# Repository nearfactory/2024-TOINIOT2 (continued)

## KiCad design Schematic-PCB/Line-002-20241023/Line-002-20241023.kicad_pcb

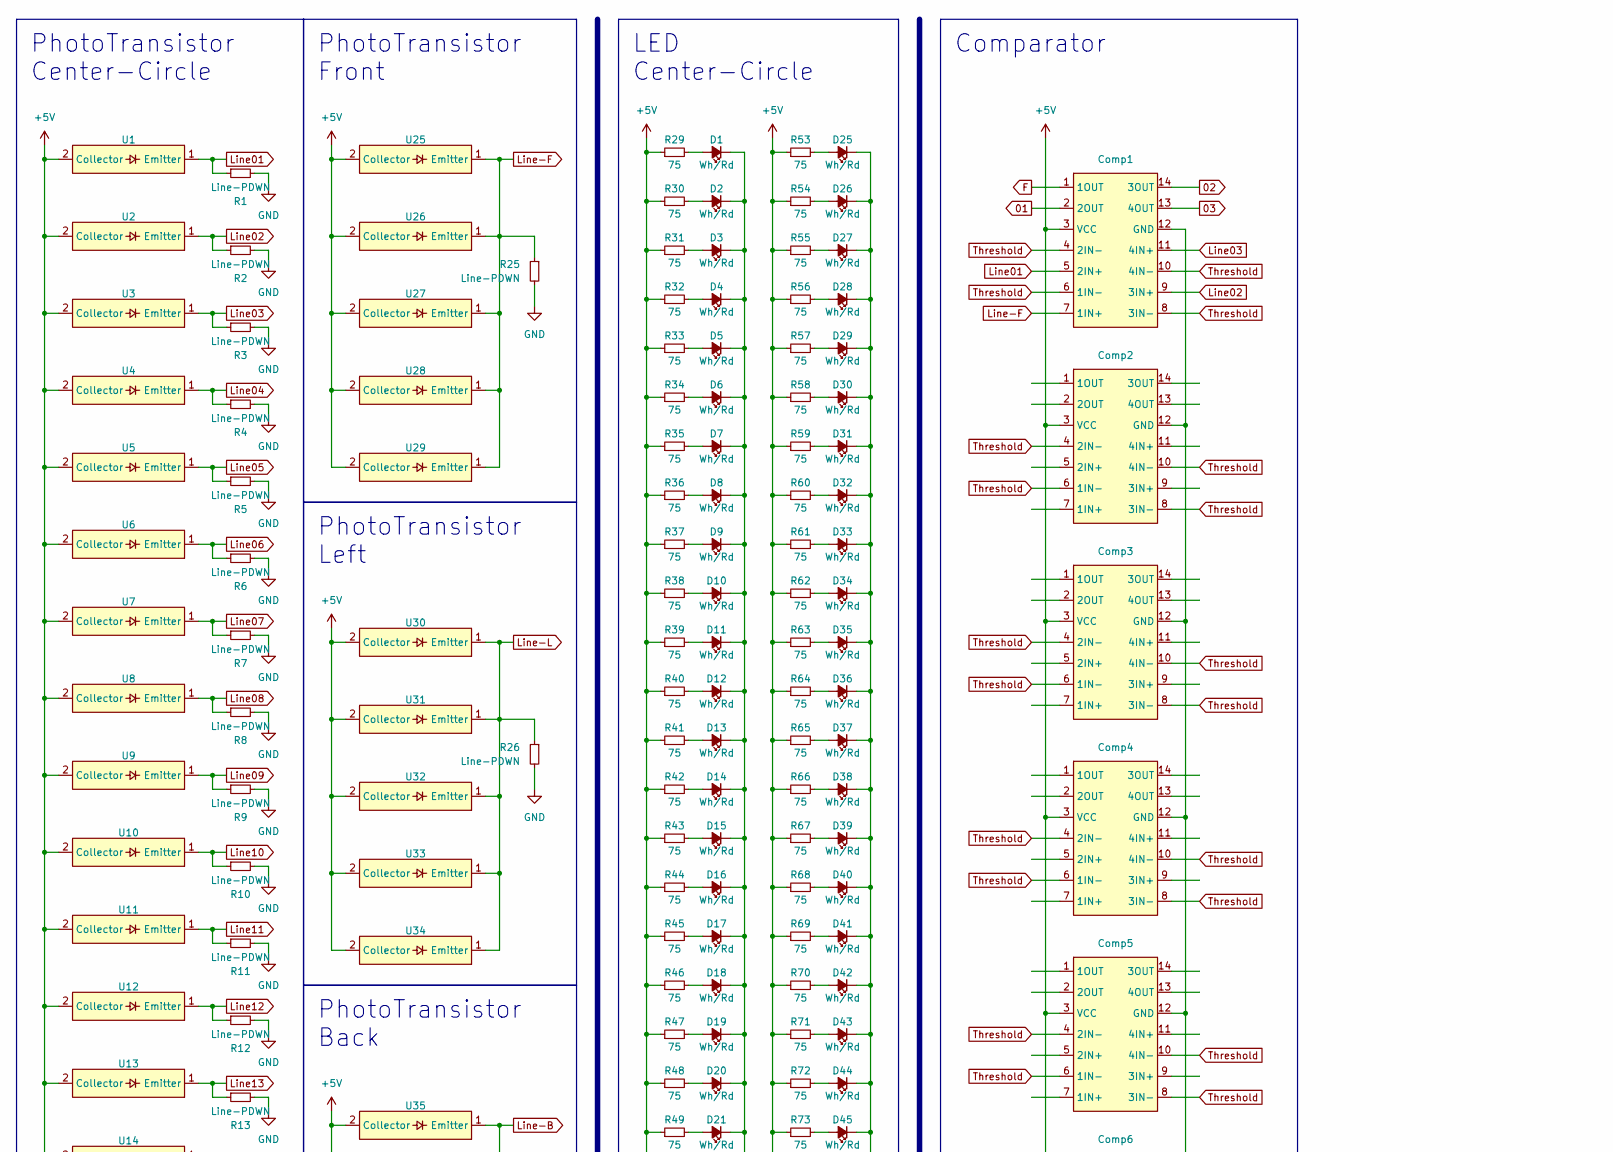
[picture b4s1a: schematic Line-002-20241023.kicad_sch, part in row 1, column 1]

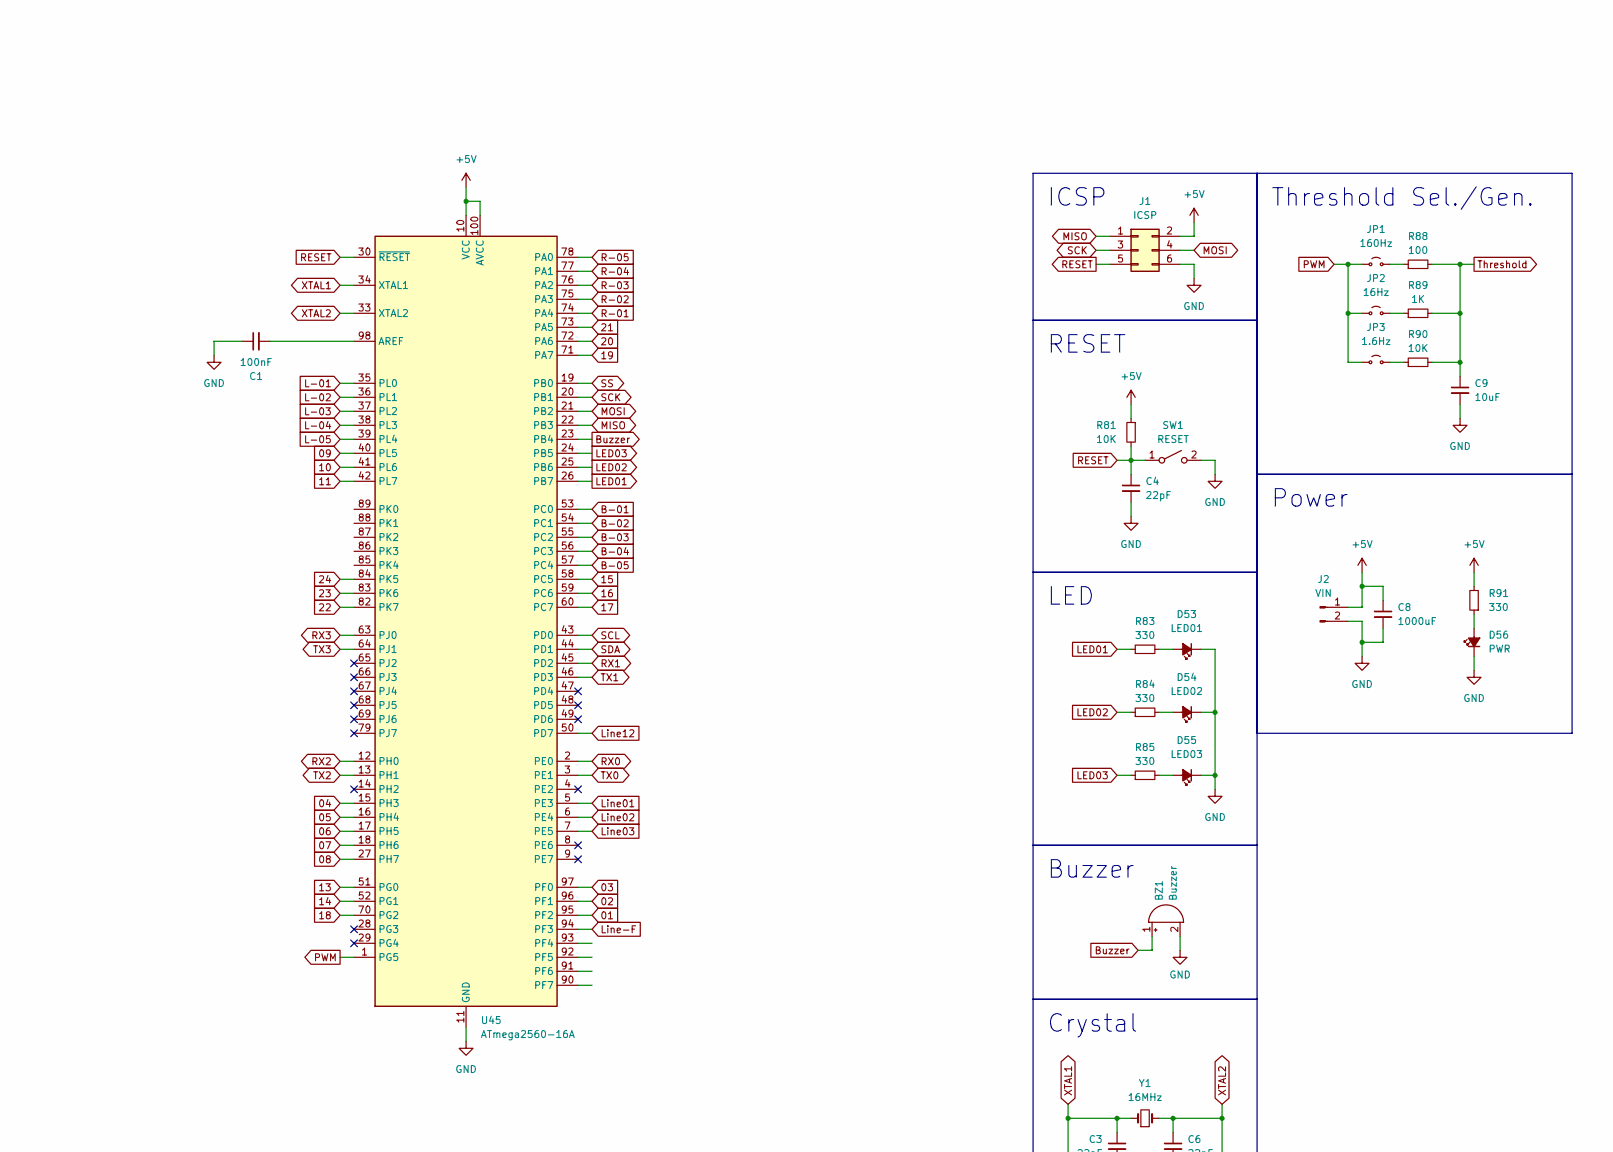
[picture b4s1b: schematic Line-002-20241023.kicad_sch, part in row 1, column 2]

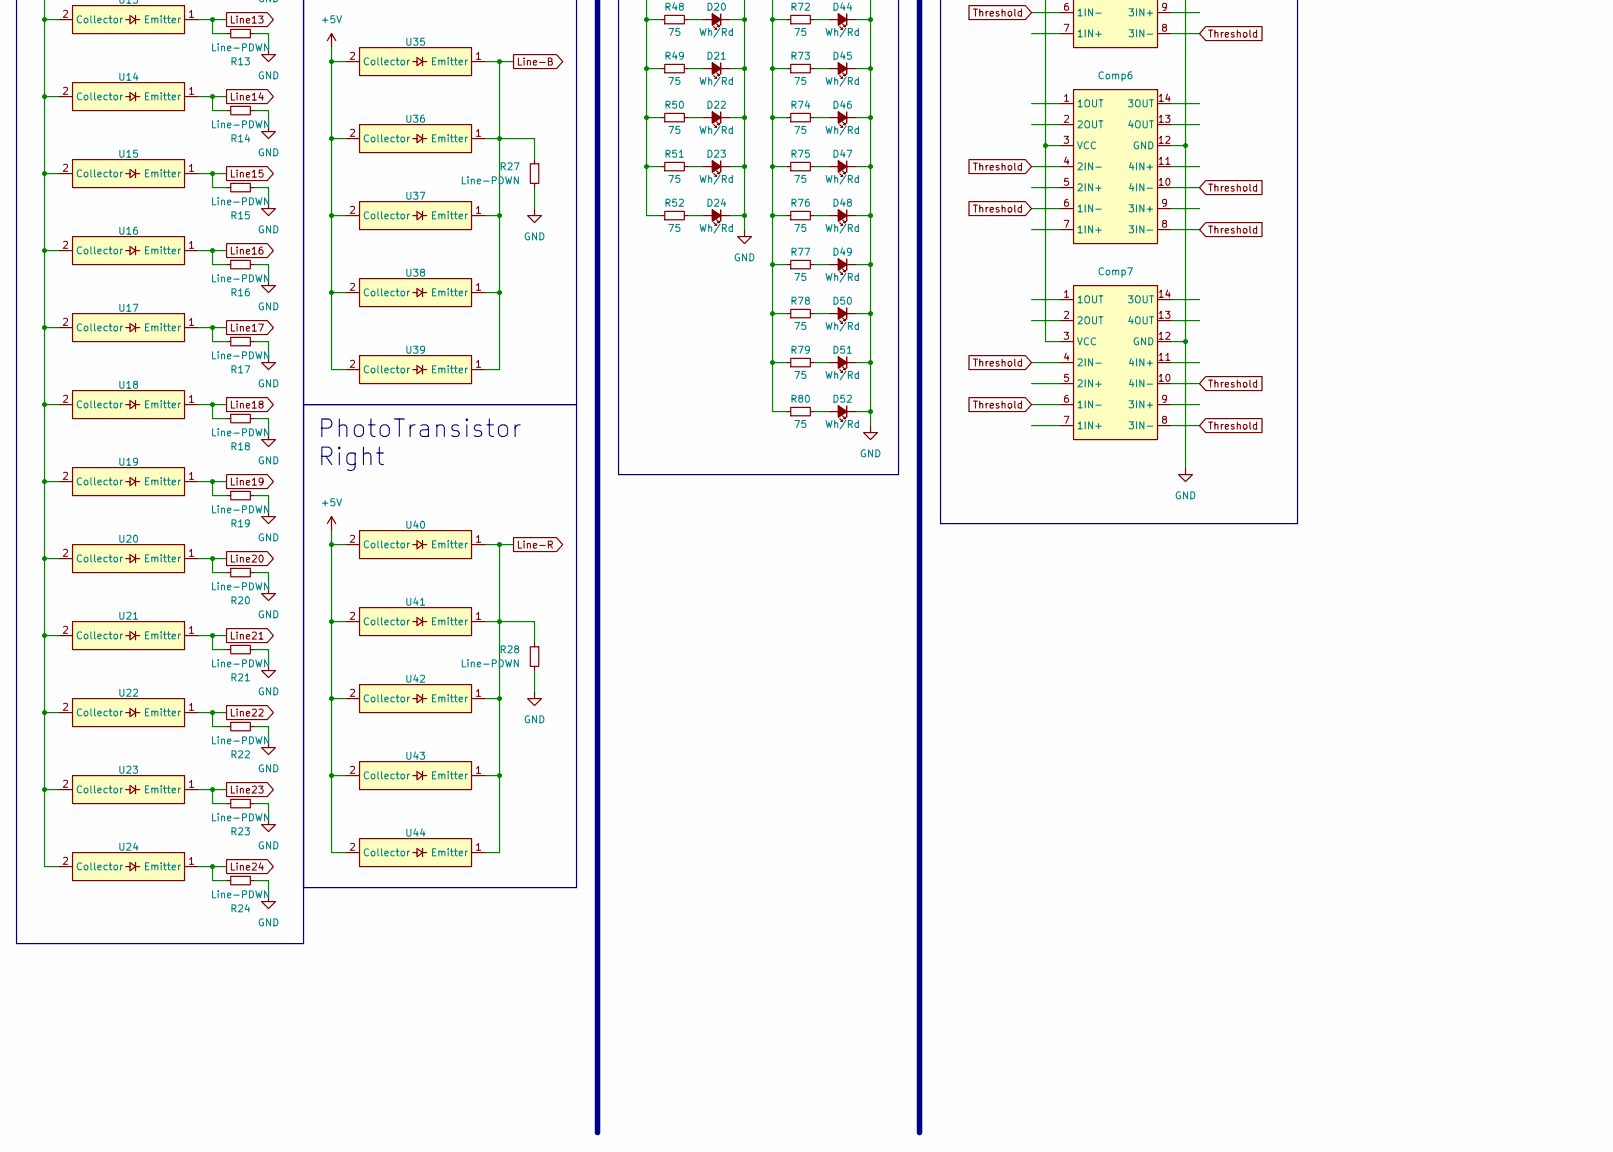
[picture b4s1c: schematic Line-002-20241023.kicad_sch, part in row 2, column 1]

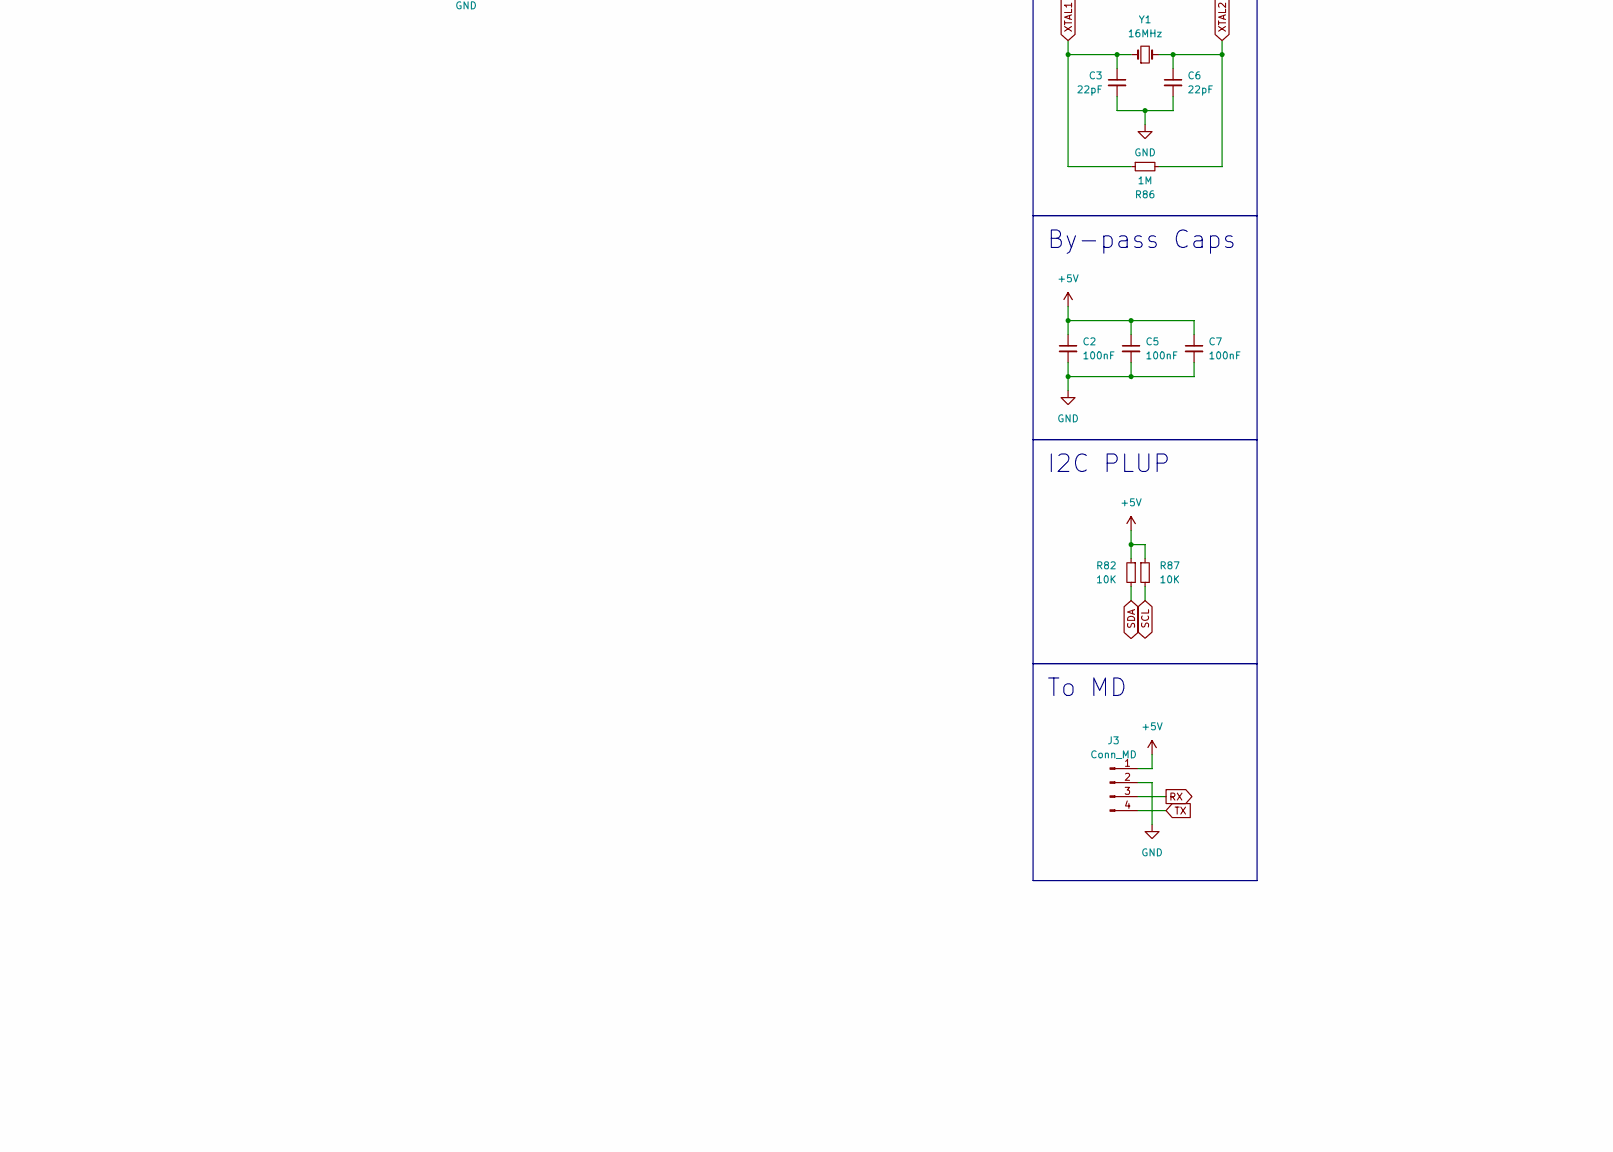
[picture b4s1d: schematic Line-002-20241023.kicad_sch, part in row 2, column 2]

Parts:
BZ1: Buzzer; PKM13EPYH4000-A0
C1, C2, C5, C7: 100nF; C_0603_1608Metric
C3, C4, C6: 22pF; C_0603_1608Metric
C8: 1000uF; C_0603_1608Metric
C9: 10uF; C_0805_2012Metric
Comp1, Comp2, Comp3, Comp4, Comp5, Comp6, Comp7: (no value)
D1, D2, D3, D4, D5, D6, D7, D8, D9, D10, D11, D12, D13, D14, D15, D16, D17, D18, D19, D20, D21, D22, D23, D24, D25, D26, D27, D28, D29, D30, D31, D32, D33, D34, D35, D36, D37, D38, D39, D40, D41, D42, D43, D44, D45, D46, D47, D48, D49, D50, D51, D52: Wh/Rd; LED-3mm
D53: LED01; LED_0603_1608Metric
D54: LED02; LED_0603_1608Metric
D55: LED03; LED_0603_1608Metric
D56: PWR; LED_0603_1608Metric
J1: ICSP; PinHeader_2x03_P2.54mm_Vertical
J2: VIN; JST_VH_B2P-VH-B_1x02_P3.96mm_Vertical
J3: Conn_MD
JP1: 160Hz; SolderJumper-2_P1.3mm_Open_Pad1.0x1.5mm
JP2: 16Hz; SolderJumper-2_P1.3mm_Open_Pad1.0x1.5mm
JP3: 1.6Hz; SolderJumper-2_P1.3mm_Open_Pad1.0x1.5mm
R1, R2, R3, R4, R5, R6, R7, R8, R9, R10, R11, R12, R13, R14, R15, R16, R17, R18, R19, R20, R21, R22, R23, R24, R25, R26, R27, R28: Line-PDWN; R_0603_1608Metric
R29, R30, R31, R32, R33, R34, R35, R36, R37, R38, R39, R40, R41, R42, R43, R44, R45, R46, R47, R48, R49, R50, R51, R52, R53, R54, R55, R56, R57, R58, R59, R60, R61, R62, R63, R64, R65, R66, R67, R68, R69, R70, R71, R72, R73, R74, R75, R76, R77, R78, R79, R80: 75; R_0603_1608Metric
R81, R82, R87, R90: 10K; R_0603_1608Metric
R83, R84, R85, R91: 330; R_0603_1608Metric
R86: 1M; R_0603_1608Metric
R88: 100; R_0603_1608Metric
R89: 1K; R_0603_1608Metric
SW1: RESET
U1, U2, U3, U4, U5, U6, U7, U8, U9, U10, U11, U12, U13, U14, U15, U16, U17, U18, U19, U20, U21, U22, U23, U24, U25, U26, U27, U28, U29, U30, U31, U32, U33, U34, U35, U36, U37, U38, U39, U40, U41, U42, U43, U44: NJL7502L
U45: ATmega2560-16A; TQFP-100_14x14mm_P0.5mm
Y1: 16MHz; AL4BT

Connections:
01: Comp1.2 (2OUT), U45.95 (PF2)
02: Comp1.14 (3OUT), U45.96 (PF1)
03: Comp1.13 (4OUT), U45.97 (PF0)
04: U45.15 (PH3)
05: U45.16 (PH4)
06: U45.17 (PH5)
07: U45.18 (PH6)
08: U45.27 (PH7)
09: U45.40 (PL5)
10: U45.41 (PL6)
11: U45.42 (PL7)
13: U45.51 (PG0)
14: U45.52 (PG1)
15: U45.58 (PC5)
16: U45.59 (PC6)
17: U45.60 (PC7)
18: U45.70 (PG2)
19: U45.71 (PA7)
20: U45.72 (PA6)
21: U45.73 (PA5)
22: U45.82 (PK7)
23: U45.83 (PK6)
24: U45.84 (PK5)
+5V: C2.1, C5.1, C7.1, C8.1, Comp1.3 (VCC), Comp2.3 (VCC), Comp3.3 (VCC), Comp4.3 (VCC), Comp5.3 (VCC), Comp6.3 (VCC), Comp7.3 (VCC), J1.2, J2.1, J3.1, R29.1, R30.1, R31.1, R32.1, R33.1, R34.1, R35.1, R36.1, R37.1, R38.1, R39.1, R40.1, R41.1, R42.1, R43.1, R44.1, R45.1, R46.1, R47.1, R48.1, R49.1, R50.1, R51.1, R52.1, R53.1, R54.1, R55.1, R56.1, R57.1, R58.1, R59.1, R60.1, R61.1, R62.1, R63.1, R64.1, R65.1, R66.1, R67.1, R68.1, R69.1, R70.1, R71.1, R72.1, R73.1, R74.1, R75.1, R76.1, R77.1, R78.1, R79.1, R80.1, R81.1, R82.1, R87.1, R91.2, U1.2 (Collector), U2.2 (Collector), U3.2 (Collector), U4.2 (Collector), U5.2 (Collector), U6.2 (Collector), U7.2 (Collector), U8.2 (Collector), U9.2 (Collector), U10.2 (Collector), U11.2 (Collector), U12.2 (Collector), U13.2 (Collector), U14.2 (Collector), U15.2 (Collector), U16.2 (Collector), U17.2 (Collector), U18.2 (Collector), U19.2 (Collector), U20.2 (Collector), U21.2 (Collector), U22.2 (Collector), U23.2 (Collector), U24.2 (Collector), U25.2 (Collector), U26.2 (Collector), U27.2 (Collector), U28.2 (Collector), U29.2 (Collector), U30.2 (Collector), U31.2 (Collector), U32.2 (Collector), U33.2 (Collector), U34.2 (Collector), U35.2 (Collector), U36.2 (Collector), U37.2 (Collector), U38.2 (Collector), U39.2 (Collector), U40.2 (Collector), U41.2 (Collector), U42.2 (Collector), U43.2 (Collector), U44.2 (Collector), U45.10 (VCC), U45.31 (VCC), U45.61 (VCC), U45.80 (VCC), U45.100 (AVCC)
B-01: U45.53 (PC0)
B-02: U45.54 (PC1)
B-03: U45.55 (PC2)
B-04: U45.56 (PC3)
B-05: U45.57 (PC4)
Buzzer: BZ1.1 (+), U45.23 (PB4)
GND: BZ1.2 (-), C1.1, C2.2, C3.2, C4.2, C5.2, C6.2, C7.2, C8.2, C9.2, Comp1.12 (GND), Comp2.12 (GND), Comp3.12 (GND), Comp4.12 (GND), Comp5.12 (GND), Comp6.12 (GND), Comp7.12 (GND), D1.1 (K), D2.1 (K), D3.1 (K), D4.1 (K), D5.1 (K), D6.1 (K), D7.1 (K), D8.1 (K), D9.1 (K), D10.1 (K), D11.1 (K), D12.1 (K), D13.1 (K), D14.1 (K), D15.1 (K), D16.1 (K), D17.1 (K), D18.1 (K), D19.1 (K), D20.1 (K), D21.1 (K), D22.1 (K), D23.1 (K), D24.1 (K), D25.1 (K), D26.1 (K), D27.1 (K), D28.1 (K), D29.1 (K), D30.1 (K), D31.1 (K), D32.1 (K), D33.1 (K), D34.1 (K), D35.1 (K), D36.1 (K), D37.1 (K), D38.1 (K), D39.1 (K), D40.1 (K), D41.1 (K), D42.1 (K), D43.1 (K), D44.1 (K), D45.1 (K), D46.1 (K), D47.1 (K), D48.1 (K), D49.1 (K), D50.1 (K), D51.1 (K), D52.1 (K), D53.1 (K), D54.1 (K), D55.1 (K), D56.1 (K), J1.6, J2.2, J3.2, R1.2, R2.2, R3.2, R4.2, R5.2, R6.2, R7.2, R8.2, R9.2, R10.2, R11.2, R12.2, R13.2, R14.2, R15.2, R16.2, R17.2, R18.2, R19.2, R20.2, R21.2, R22.2, R23.2, R24.2, R25.2, R26.2, R27.2, R28.2, SW1.2 (B), U45.11 (GND), U45.32 (GND), U45.62 (GND), U45.81 (GND), U45.99 (GND)
L-01: U45.35 (PL0)
L-02: U45.36 (PL1)
L-03: U45.37 (PL2)
L-04: U45.38 (PL3)
L-05: U45.39 (PL4)
LED01: R83.1, U45.26 (PB7)
LED02: R84.1, U45.25 (PB6)
LED03: R85.1, U45.24 (PB5)
Line01: Comp1.5 (2IN+), R1.1, U1.1 (Emitter), U45.5 (PE3)
Line02: Comp1.9 (3IN+), R2.1, U2.1 (Emitter), U45.6 (PE4)
Line03: Comp1.11 (4IN+), R3.1, U3.1 (Emitter), U45.7 (PE5)
Line04: R4.1, U4.1 (Emitter)
Line05: R5.1, U5.1 (Emitter)
Line06: R6.1, U6.1 (Emitter)
Line07: R7.1, U7.1 (Emitter)
Line08: R8.1, U8.1 (Emitter)
Line09: R9.1, U9.1 (Emitter)
Line10: R10.1, U10.1 (Emitter)
Line11: R11.1, U11.1 (Emitter)
Line12: R12.1, U12.1 (Emitter), U45.50 (PD7)
Line13: R13.1, U13.1 (Emitter)
Line14: R14.1, U14.1 (Emitter)
Line15: R15.1, U15.1 (Emitter)
Line16: R16.1, U16.1 (Emitter)
Line17: R17.1, U17.1 (Emitter)
Line18: R18.1, U18.1 (Emitter)
Line19: R19.1, U19.1 (Emitter)
Line20: R20.1, U20.1 (Emitter)
Line21: R21.1, U21.1 (Emitter)
Line22: R22.1, U22.1 (Emitter)
Line23: R23.1, U23.1 (Emitter)
Line24: R24.1, U24.1 (Emitter)
Line-B: R27.1, U35.1 (Emitter), U36.1 (Emitter), U37.1 (Emitter), U38.1 (Emitter), U39.1 (Emitter)
Line-F: Comp1.7 (1IN+), R25.1, U25.1 (Emitter), U26.1 (Emitter), U27.1 (Emitter), U28.1 (Emitter), U29.1 (Emitter), U45.94 (PF3)
Line-L: R26.1, U30.1 (Emitter), U31.1 (Emitter), U32.1 (Emitter), U33.1 (Emitter), U34.1 (Emitter)
Line-R: R28.1, U40.1 (Emitter), U41.1 (Emitter), U42.1 (Emitter), U43.1 (Emitter), U44.1 (Emitter)
MISO: J1.1, U45.22 (PB3)
MOSI: J1.4, U45.21 (PB2)
unnamed: D1.2 (A), R29.2
unnamed: D2.2 (A), R30.2
unnamed: D3.2 (A), R31.2
unnamed: D4.2 (A), R32.2
unnamed: D5.2 (A), R33.2
unnamed: D6.2 (A), R34.2
unnamed: D7.2 (A), R35.2
unnamed: D8.2 (A), R36.2
unnamed: D9.2 (A), R37.2
unnamed: D10.2 (A), R38.2
unnamed: D11.2 (A), R39.2
unnamed: D12.2 (A), R40.2
unnamed: D13.2 (A), R41.2
unnamed: D14.2 (A), R42.2
unnamed: D15.2 (A), R43.2
unnamed: D16.2 (A), R44.2
unnamed: D17.2 (A), R45.2
unnamed: D18.2 (A), R46.2
unnamed: D19.2 (A), R47.2
unnamed: D20.2 (A), R48.2
unnamed: D21.2 (A), R49.2
unnamed: D22.2 (A), R50.2
unnamed: D23.2 (A), R51.2
unnamed: D24.2 (A), R52.2
unnamed: D25.2 (A), R53.2
unnamed: D26.2 (A), R54.2
unnamed: D27.2 (A), R55.2
unnamed: D28.2 (A), R56.2
unnamed: D29.2 (A), R57.2
unnamed: D30.2 (A), R58.2
unnamed: D31.2 (A), R59.2
unnamed: D32.2 (A), R60.2
unnamed: D33.2 (A), R61.2
unnamed: D34.2 (A), R62.2
unnamed: D35.2 (A), R63.2
unnamed: D36.2 (A), R64.2
unnamed: D37.2 (A), R65.2
unnamed: D38.2 (A), R66.2
unnamed: D39.2 (A), R67.2
unnamed: D40.2 (A), R68.2
unnamed: D41.2 (A), R69.2
unnamed: D42.2 (A), R70.2
unnamed: D43.2 (A), R71.2
unnamed: D44.2 (A), R72.2
unnamed: D45.2 (A), R73.2
unnamed: D46.2 (A), R74.2
unnamed: D47.2 (A), R75.2
unnamed: D48.2 (A), R76.2
unnamed: D49.2 (A), R77.2
unnamed: D50.2 (A), R78.2
unnamed: D51.2 (A), R79.2
unnamed: D52.2 (A), R80.2
unnamed: D53.2 (A), R83.2
unnamed: D54.2 (A), R84.2
unnamed: D55.2 (A), R85.2
unnamed: D56.2 (A), R91.1
unnamed: JP1.2 (B), R88.1
unnamed: JP2.2 (B), R89.1
unnamed: JP3.2 (B), R90.1
unnamed: C1.2, U45.98 (AREF)
PWM: JP1.1 (A), JP2.1 (A), JP3.1 (A), U45.1 (PG5)
R-01: U45.74 (PA4)
R-02: U45.75 (PA3)
R-03: U45.76 (PA2)
R-04: U45.77 (PA1)
R-05: U45.78 (PA0)
RESET: C4.1, J1.5, R81.2, SW1.1 (A), U45.30 (~RESET)
RX0: U45.2 (PE0)
RX1: U45.45 (PD2)
RX2: U45.12 (PH0)
RX3: U45.63 (PJ0)
SCK: J1.3, U45.20 (PB1)
SCL: R87.2, U45.43 (PD0)
SDA: R82.2, U45.44 (PD1)
SS: U45.19 (PB0)
TX0: U45.3 (PE1)
TX1: U45.46 (PD3)
TX2: U45.13 (PH1)
TX3: U45.64 (PJ1)
Threshold: C9.1, Comp1.4 (2IN-), Comp1.6 (1IN-), Comp1.8 (3IN-), Comp1.10 (4IN-), Comp2.4 (2IN-), Comp2.6 (1IN-), Comp2.8 (3IN-), Comp2.10 (4IN-), Comp3.4 (2IN-), Comp3.6 (1IN-), Comp3.8 (3IN-), Comp3.10 (4IN-), Comp4.4 (2IN-), Comp4.6 (1IN-), Comp4.8 (3IN-), Comp4.10 (4IN-), Comp5.4 (2IN-), Comp5.6 (1IN-), Comp5.8 (3IN-), Comp5.10 (4IN-), Comp6.4 (2IN-), Comp6.6 (1IN-), Comp6.8 (3IN-), Comp6.10 (4IN-), Comp7.4 (2IN-), Comp7.6 (1IN-), Comp7.8 (3IN-), Comp7.10 (4IN-), R88.2, R89.2, R90.2
XTAL1: C3.1, R86.1, U45.34 (XTAL1), Y1.1
XTAL2: C6.1, R86.2, U45.33 (XTAL2), Y1.2

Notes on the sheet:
By-pass Caps
PhotoTransistor Back
Buzzer
LED Center-Circle
PhotoTransistor Front
PhotoTransistor Center-Circle
Crystal
I2C PLUP
Threshold Sel./Gen.
RESET
LED
Comparator
ICSP
Power
PhotoTransistor Right
PhotoTransistor Left
To MD

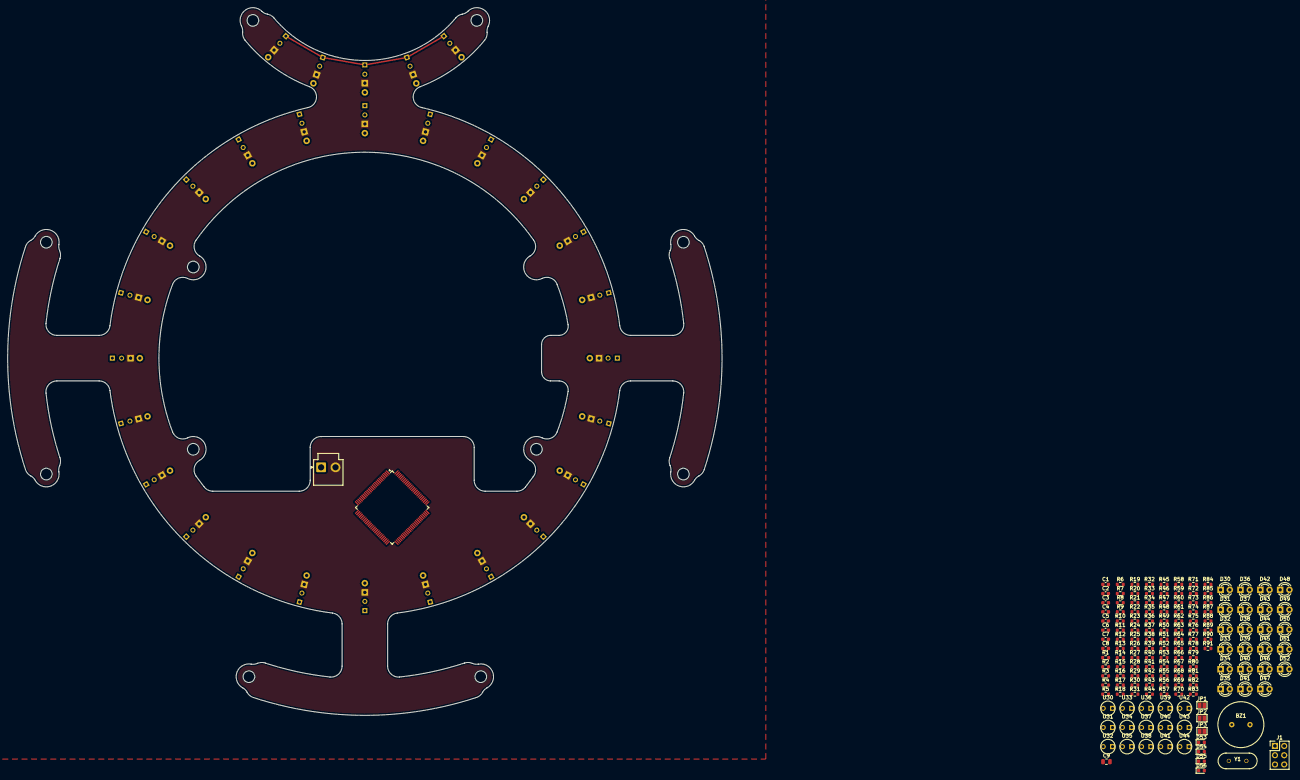
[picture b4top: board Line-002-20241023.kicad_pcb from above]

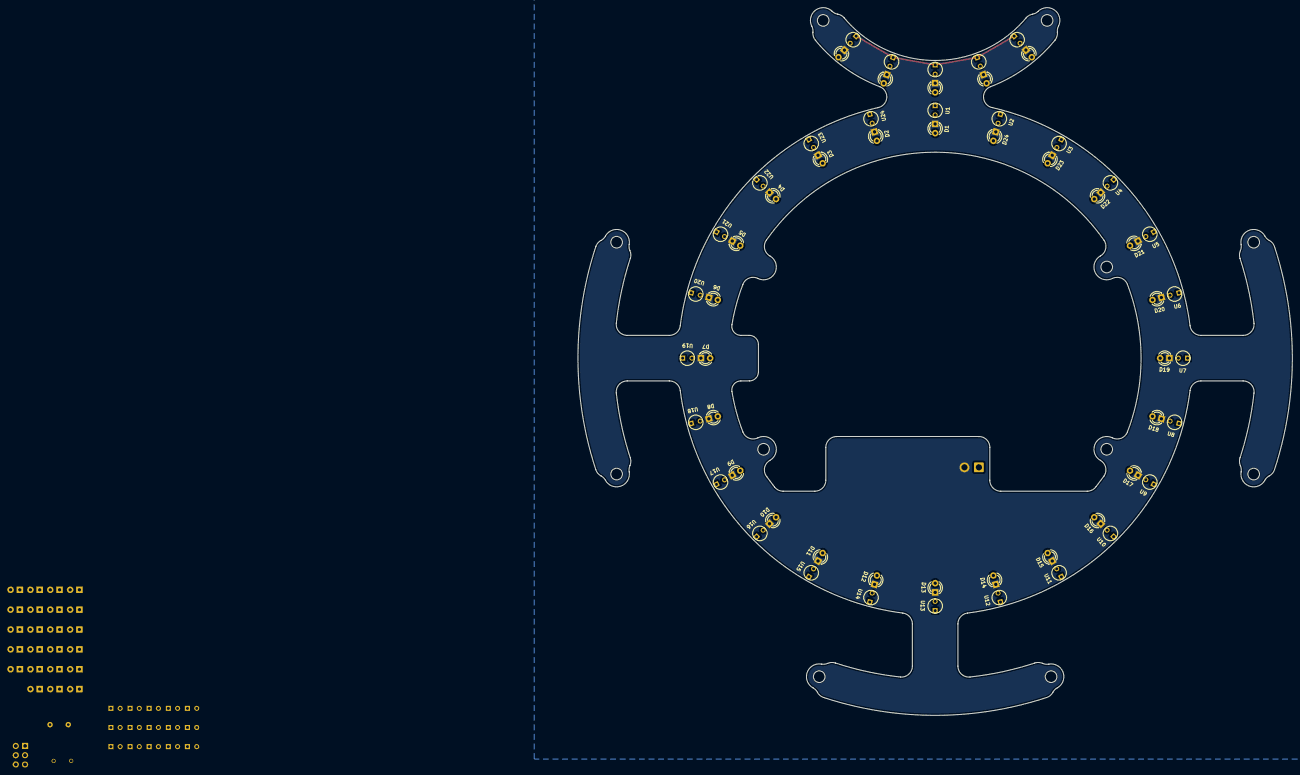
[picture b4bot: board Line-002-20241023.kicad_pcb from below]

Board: 4 copper layers, 196.0 x 194.2 mm, 208 parts (58 on the bottom side), 104 nets.

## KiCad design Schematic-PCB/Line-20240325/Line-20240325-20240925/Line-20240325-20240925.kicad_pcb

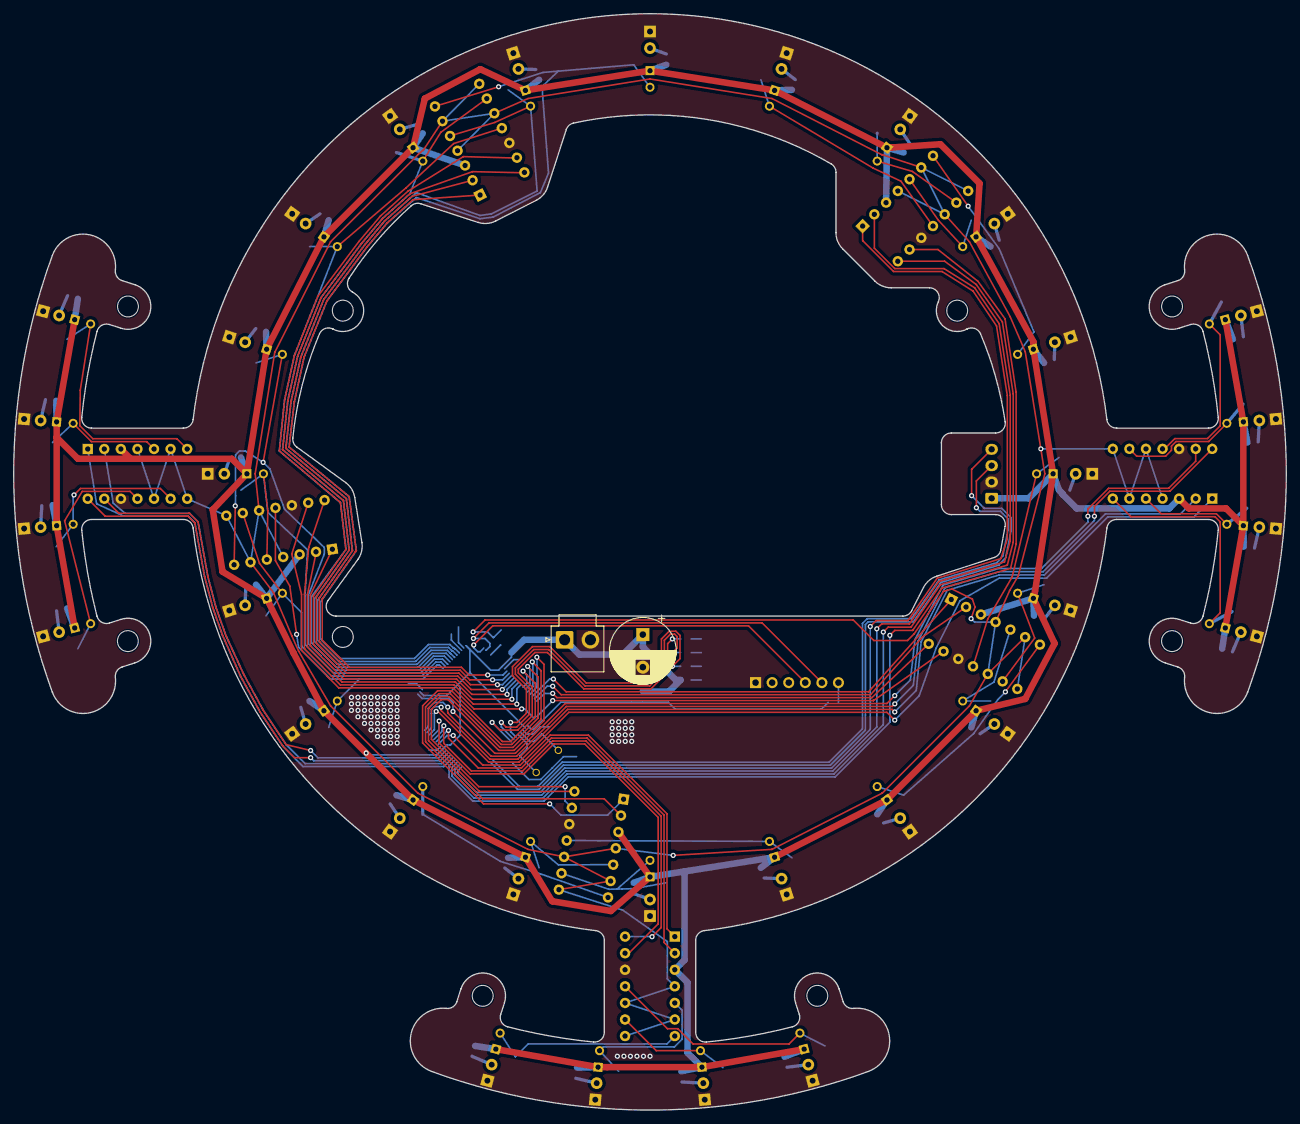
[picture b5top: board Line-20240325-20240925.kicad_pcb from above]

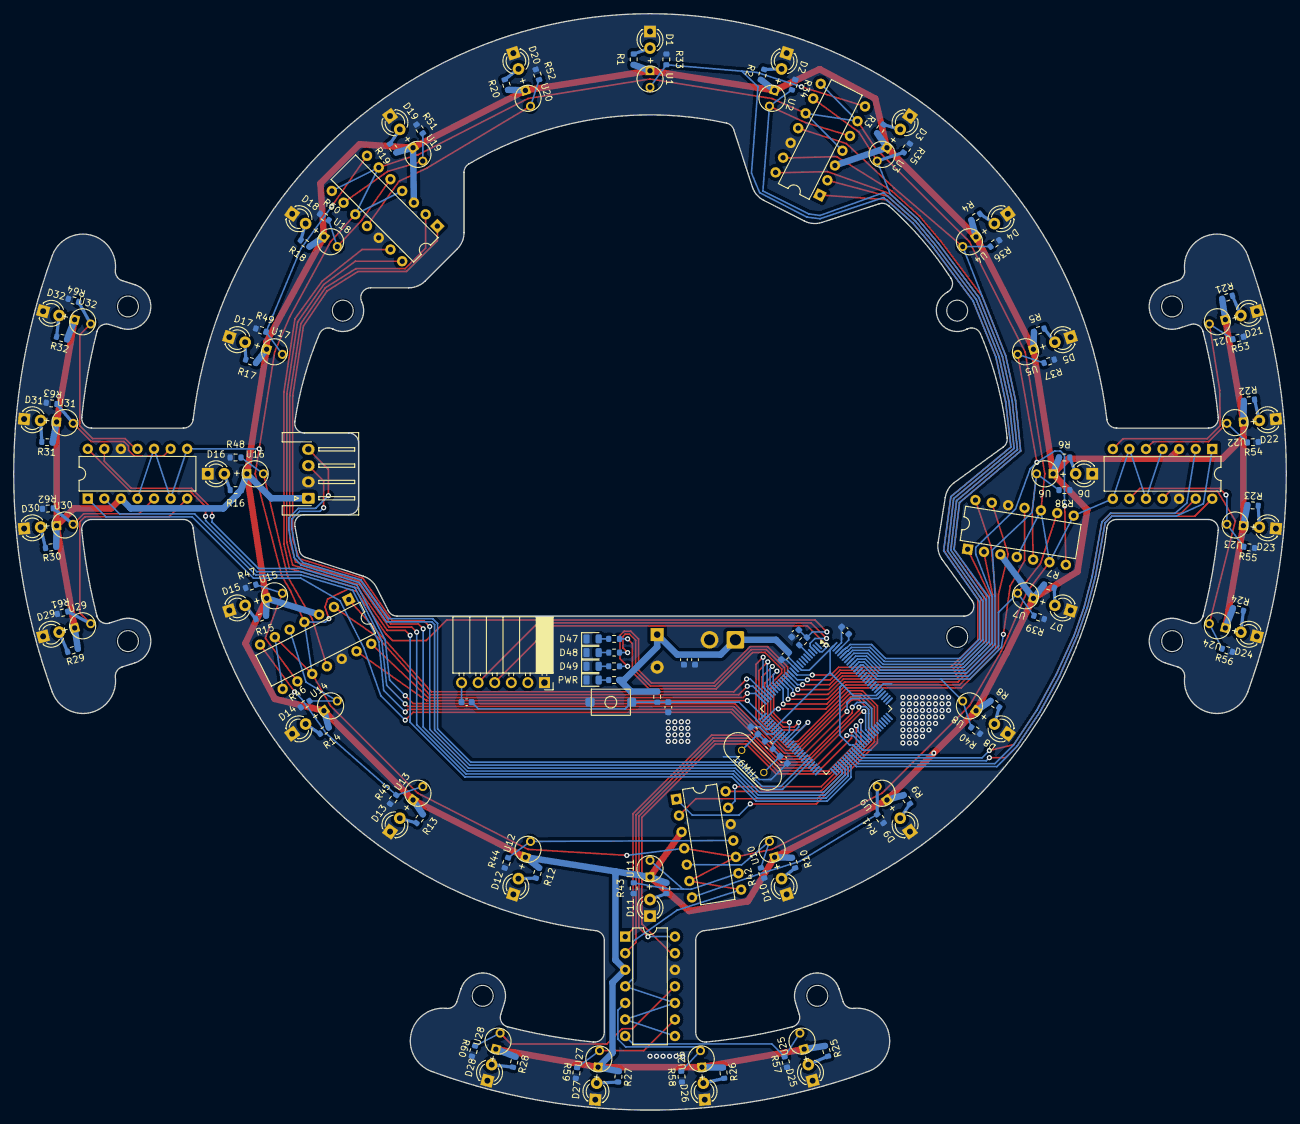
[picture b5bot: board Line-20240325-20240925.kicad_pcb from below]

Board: 2 copper layers, 195.0 x 168.0 mm, 163 parts (161 on the bottom side), 116 nets.

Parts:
C1: 100uF; CP_Radial_D10.0mm_P5.00mm
C2: 10uF; C_0603_1608Metric
C3, C4, C5, C8: 0.1uF; C_0603_1608Metric
C6, C7, C9: 22pF; C_0603_1608Metric
C10: LPF; C_0603_1608Metric
Comp1, Comp2, Comp3, Comp4, Comp5, Comp6, Comp7, Comp8: LM339
D1, D2, D3, D4, D5, D6, D7, D8, D9, D10, D11, D12, D13, D14, D15, D16, D17, D18, D19, D20, D21, D22, D23, D24, D25, D26, D27, D28, D29, D30, D31, D32: LED_Small; LED-3mm
D33: POWER; LED_0805_2012Metric
D34: LED3; LED_0805_2012Metric
D35: LED2; LED_0805_2012Metric
D36: LED1; LED_0805_2012Metric
J1: Conn_01x02_Pin; JST_VH_B2P-VH-B_1x02_P3.96mm_Vertical
J2: Conn_01x04_Pin; JST_XH_S4B-XH-A-1_1x04_P2.50mm_Horizontal
J3: Conn_01x06_Pin; PinSocket_1x06_P2.54mm_Horizontal
R1, R2, R3, R4, R5, R6, R7, R8, R9, R10, R11, R12, R13, R14, R15, R16, R17, R18, R19, R20, R21, R22, R23, R24, R25, R26, R27, R28, R29, R30, R31, R32: 75; R_0603_1608Metric
R33, R34, R35, R36, R37, R38, R39, R40, R41, R42, R43, R44, R45, R46, R47, R48, R49, R50, R51, R52, R53, R54, R55, R56, R57, R58, R59, R60, R61, R62, R63, R64: Line-Pulldown; R_0603_1608Metric
R65, R67, R69, R70: 330; R_0603_1608Metric
R66: 1M; R_0603_1608Metric
R71: 10K; R_0603_1608Metric
R72: LPF; R_0603_1608Metric
SW1: SW_Push; Tactile1
U1, U2, U3, U4, U5, U6, U7, U8, U9, U10, U11, U12, U13, U14, U15, U16, U17, U18, U19, U20, U21, U22, U23, U24, U25, U26, U27, U28, U29, U30, U31, U32: NJL7502L
U33: ATmega2560-16A; TQFP-100_14x14mm_P0.5mm
Y1: 16MHz; AL4BT

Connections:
+5V: C1.1, C2.1, C3.1, C4.1, Comp1.3 (VCC), Comp2.3 (VCC), Comp3.3 (VCC), Comp4.3 (VCC), Comp5.3 (VCC), Comp6.3 (VCC), Comp7.3 (VCC), Comp8.3 (VCC), J1.1, J2.1, R1.2, R2.2, R3.2, R4.2, R5.2, R6.2, R7.2, R8.2, R9.2, R10.2, R11.2, R12.2, R13.2, R14.2, R15.2, R16.2, R17.2, R18.2, R19.2, R20.2, R21.2, R22.2, R23.2, R24.2, R25.2, R26.2, R27.2, R28.2, R29.2, R30.2, R31.2, R32.2, R65.1, R71.1, U1.2 (Collector), U2.2 (Collector), U3.2 (Collector), U4.2 (Collector), U5.2 (Collector), U6.2 (Collector), U7.2 (Collector), U8.2 (Collector), U9.2 (Collector), U10.2 (Collector), U11.2 (Collector), U12.2 (Collector), U13.2 (Collector), U14.2 (Collector), U15.2 (Collector), U16.2 (Collector), U17.2 (Collector), U18.2 (Collector), U19.2 (Collector), U20.2 (Collector), U21.2 (Collector), U22.2 (Collector), U23.2 (Collector), U24.2 (Collector), U25.2 (Collector), U26.2 (Collector), U27.2 (Collector), U28.2 (Collector), U29.2 (Collector), U30.2 (Collector), U31.2 (Collector), U32.2 (Collector), U33.10 (VCC), U33.31 (VCC), U33.61 (VCC), U33.80 (VCC), U33.100 (AVCC)
GND: C1.2, C2.2, C3.2, C4.2, C5.1, C6.1, C7.1, C9.2, C10.2, Comp1.12 (GND), Comp2.12 (GND), Comp3.12 (GND), Comp4.12 (GND), Comp5.12 (GND), Comp6.12 (GND), Comp7.12 (GND), Comp8.12 (GND), D1.1 (K), D2.1 (K), D3.1 (K), D4.1 (K), D5.1 (K), D6.1 (K), D7.1 (K), D8.1 (K), D9.1 (K), D10.1 (K), D11.1 (K), D12.1 (K), D13.1 (K), D14.1 (K), D15.1 (K), D16.1 (K), D17.1 (K), D18.1 (K), D19.1 (K), D20.1 (K), D21.1 (K), D22.1 (K), D23.1 (K), D24.1 (K), D25.1 (K), D26.1 (K), D27.1 (K), D28.1 (K), D29.1 (K), D30.1 (K), D31.1 (K), D32.1 (K), D33.1 (K), D34.1 (K), D35.1 (K), D36.1 (K), J1.2, J2.2, J3.1, R33.2, R34.2, R35.2, R36.2, R37.2, R38.2, R39.2, R40.2, R41.2, R42.2, R43.2, R44.2, R45.2, R46.2, R47.2, R48.2, R49.2, R50.2, R51.2, R52.2, R53.2, R54.2, R55.2, R56.2, R57.2, R58.2, R59.2, R60.2, R61.2, R62.2, R63.2, R64.2, SW1.2, U33.11 (GND), U33.32 (GND), U33.62 (GND), U33.81 (GND), U33.99 (GND)
Line01: Comp1.1 (1OUT), U33.12 (PH0/D17/RX2)
Line02: Comp1.2 (2OUT), U33.13 (PH1/D16/TX2)
Line03: Comp1.14 (3OUT), U33.14 (PH2)
Line04: Comp1.13 (4OUT), U33.15 (PH3/D6)
Line05: Comp2.1 (1OUT), U33.16 (PH4/D7)
Line06: Comp2.2 (2OUT), U33.17 (PH5/D8)
Line07: Comp2.14 (3OUT), U33.18 (PH6/D9)
Line08: Comp2.13 (4OUT), U33.27 (PH7)
Line09: Comp3.1 (1OUT), U33.19 (PB0/D53/SS)
Line10: Comp3.2 (2OUT), U33.20 (PB1/D52/SCK)
Line11: Comp3.14 (3OUT), U33.21 (PB2/D51/MOSI)
Line12: Comp3.13 (4OUT), U33.22 (PB3/D50/MISO)
Line13: Comp4.1 (1OUT), U33.23 (PB4/D10)
Line14: Comp4.2 (2OUT), U33.24 (PB5/D11)
Line15: Comp4.14 (3OUT), U33.25 (PB6/D12)
Line16: Comp4.13 (4OUT), U33.26 (PB7/D13)
Line17: Comp5.1 (1OUT), U33.53 (PC0/D37)
Line18: Comp5.2 (2OUT), U33.54 (PC1/D36)
Line19: Comp5.14 (3OUT), U33.55 (PC2/D35)
Line20: Comp5.13 (4OUT), U33.56 (PC3/D34)
Line21: Comp6.1 (1OUT), U33.57 (PC4/D33)
Line22: Comp6.2 (2OUT), U33.58 (PC5/D32)
Line23: Comp6.14 (3OUT), U33.59 (PC6/D31)
Line24: Comp6.13 (4OUT), U33.60 (PC7/D30)
Line25: Comp7.1 (1OUT), U33.63 (PJ0/D15/RX3)
Line26: Comp7.2 (2OUT), U33.64 (PJ1/D14/TX3)
Line27: Comp7.14 (3OUT), U33.65 (PJ2)
Line28: Comp7.13 (4OUT), U33.66 (PJ3)
Line29: Comp8.1 (1OUT), U33.67 (PJ4)
Line30: Comp8.2 (2OUT), U33.68 (PJ5)
Line31: Comp8.14 (3OUT), U33.69 (PJ6)
Line32: Comp8.13 (4OUT), U33.79 (PJ7)
Line-MD-Main=RX_5V: J2.4, U33.46 (PD3/D18/TX1)
Line-MD-Main=TX_5V: J2.3, U33.45 (PD2/D19/RX1)
LineThreshold: C10.1, Comp1.4 (2IN-), Comp1.6 (1IN-), Comp1.8 (3IN-), Comp1.10 (4IN-), Comp2.4 (2IN-), Comp2.6 (1IN-), Comp2.8 (3IN-), Comp2.10 (4IN-), Comp3.4 (2IN-), Comp3.6 (1IN-), Comp3.8 (3IN-), Comp3.10 (4IN-), Comp4.4 (2IN-), Comp4.6 (1IN-), Comp4.8 (3IN-), Comp4.10 (4IN-), Comp5.4 (2IN-), Comp5.6 (1IN-), Comp5.8 (3IN-), Comp5.10 (4IN-), Comp6.4 (2IN-), Comp6.6 (1IN-), Comp6.8 (3IN-), Comp6.10 (4IN-), Comp7.4 (2IN-), Comp7.6 (1IN-), Comp7.8 (3IN-), Comp7.10 (4IN-), Comp8.4 (2IN-), Comp8.6 (1IN-), Comp8.8 (3IN-), Comp8.10 (4IN-), R72.2
unnamed: D1.2 (A), R1.1
unnamed: D2.2 (A), R2.1
unnamed: D3.2 (A), R3.1
unnamed: D4.2 (A), R4.1
unnamed: D5.2 (A), R5.1
unnamed: D6.2 (A), R6.1
unnamed: D7.2 (A), R7.1
unnamed: D8.2 (A), R8.1
unnamed: D9.2 (A), R9.1
unnamed: D10.2 (A), R10.1
unnamed: D11.2 (A), R11.1
unnamed: D12.2 (A), R12.1
unnamed: D13.2 (A), R13.1
unnamed: D14.2 (A), R14.1
unnamed: D15.2 (A), R15.1
unnamed: D16.2 (A), R16.1
unnamed: D17.2 (A), R17.1
unnamed: D18.2 (A), R18.1
unnamed: D19.2 (A), R19.1
unnamed: D20.2 (A), R20.1
unnamed: D21.2 (A), R21.1
unnamed: D22.2 (A), R22.1
unnamed: D23.2 (A), R23.1
unnamed: D24.2 (A), R24.1
unnamed: D25.2 (A), R25.1
unnamed: D26.2 (A), R26.1
unnamed: D27.2 (A), R27.1
unnamed: D28.2 (A), R28.1
unnamed: D29.2 (A), R29.1
unnamed: D30.2 (A), R30.1
unnamed: D31.2 (A), R31.1
unnamed: D32.2 (A), R32.1
unnamed: D33.2 (A), R65.2
unnamed: D34.2 (A), R67.1
unnamed: D35.2 (A), R69.1
unnamed: D36.2 (A), R70.1
unnamed: C8.1, J3.6
unnamed: C5.2, U33.98 (AREF)
unnamed: R72.1, U33.5 (PE3/D5)
unnamed: R70.2, U33.35 (PL0/D49)
unnamed: R69.2, U33.36 (PL1/D48)
unnamed: R67.2, U33.37 (PL2/D47)
unnamed: C6.2, R66.2, U33.34 (XTAL1), Y1.2
unnamed: C7.2, R66.1, U33.33 (XTAL2), Y1.1
RESET: C8.2, C9.1, R71.2, SW1.1, U33.30 (~RESET)
RX-USB: J3.5, U33.3 (PE1/D1/TX0)
Raw1: Comp1.7 (1IN+), R33.1, U1.1 (Emitter), U33.97 (PF0/ADC0)
Raw2: Comp1.5 (2IN+), R34.1, U2.1 (Emitter), U33.96 (PF1/ADC1)
Raw3: Comp1.9 (3IN+), R35.1, U3.1 (Emitter), U33.95 (PF2/ADC2)
Raw4: Comp1.11 (4IN+), R36.1, U4.1 (Emitter), U33.94 (PF3/ADC3)
Raw5: Comp2.7 (1IN+), R37.1, U5.1 (Emitter), U33.93 (PF4/ADC4)
Raw6: Comp2.5 (2IN+), R38.1, U6.1 (Emitter), U33.92 (PF5/ADC5)
Raw7: Comp2.9 (3IN+), R39.1, U7.1 (Emitter), U33.91 (PF6/ADC6)
Raw8: Comp2.11 (4IN+), R40.1, U8.1 (Emitter), U33.90 (PF7/ADC7)
Raw9: Comp3.7 (1IN+), R41.1, U9.1 (Emitter)
Raw10: Comp3.5 (2IN+), R42.1, U10.1 (Emitter)
Raw11: Comp3.9 (3IN+), R43.1, U11.1 (Emitter)
Raw12: Comp3.11 (4IN+), R44.1, U12.1 (Emitter)
Raw13: Comp4.7 (1IN+), R45.1, U13.1 (Emitter)
Raw14: Comp4.5 (2IN+), R46.1, U14.1 (Emitter)
Raw15: Comp4.9 (3IN+), R47.1, U15.1 (Emitter)
Raw16: Comp4.11 (4IN+), R48.1, U16.1 (Emitter)
Raw17: Comp5.7 (1IN+), R49.1, U17.1 (Emitter)
Raw18: Comp5.5 (2IN+), R50.1, U18.1 (Emitter)
Raw19: Comp5.9 (3IN+), R51.1, U19.1 (Emitter)
Raw20: Comp5.11 (4IN+), R52.1, U20.1 (Emitter)
Raw21: Comp6.7 (1IN+), R53.1, U21.1 (Emitter)
Raw22: Comp6.5 (2IN+), R54.1, U22.1 (Emitter)
Raw23: Comp6.9 (3IN+), R55.1, U23.1 (Emitter)
Raw24: Comp6.11 (4IN+), R56.1, U24.1 (Emitter)
Raw25: Comp7.7 (1IN+), R57.1, U25.1 (Emitter)
Raw26: Comp7.5 (2IN+), R58.1, U26.1 (Emitter)
Raw27: Comp7.9 (3IN+), R59.1, U27.1 (Emitter)
Raw28: Comp7.11 (4IN+), R60.1, U28.1 (Emitter)
Raw29: Comp8.7 (1IN+), R61.1, U29.1 (Emitter)
Raw30: Comp8.5 (2IN+), R62.1, U30.1 (Emitter)
Raw31: Comp8.9 (3IN+), R63.1, U31.1 (Emitter)
Raw32: Comp8.11 (4IN+), R64.1, U32.1 (Emitter)
TX-USB: J3.4, U33.2 (PE0/D0/RX0)
